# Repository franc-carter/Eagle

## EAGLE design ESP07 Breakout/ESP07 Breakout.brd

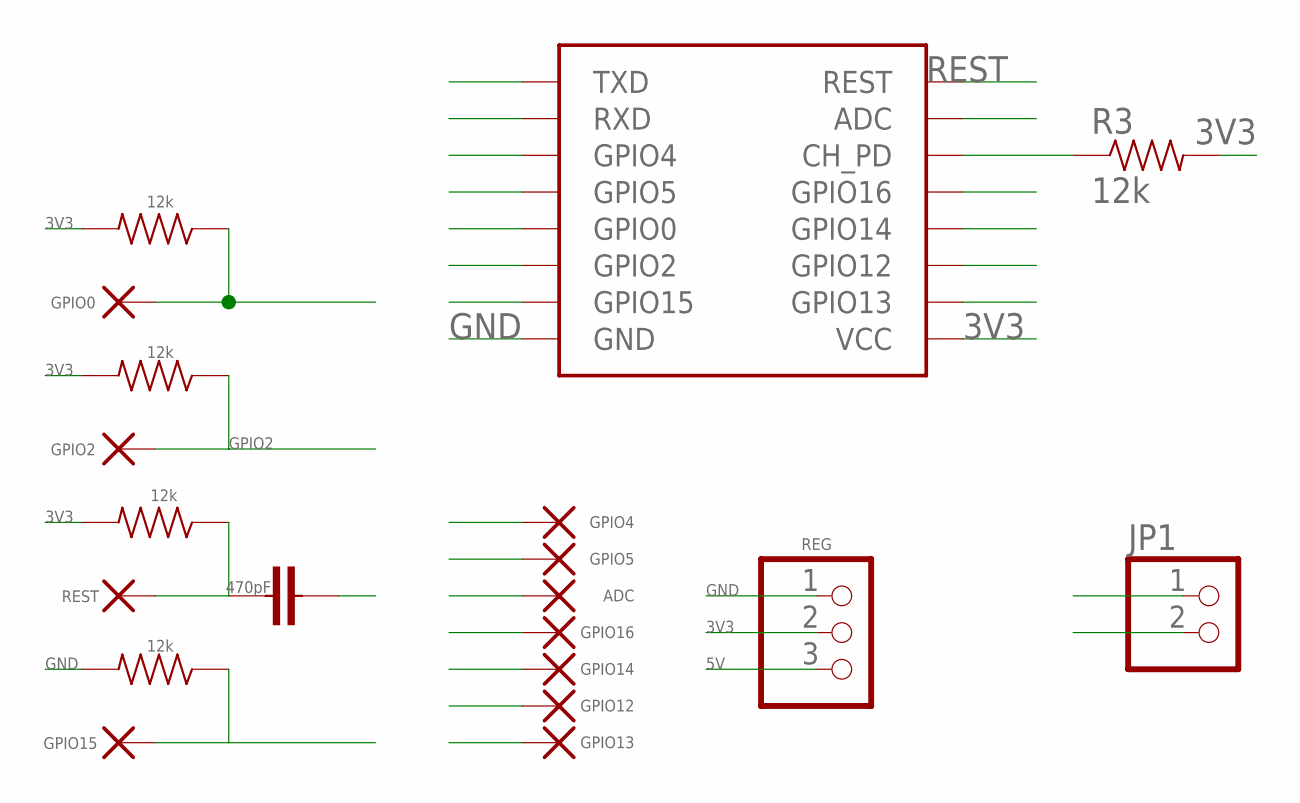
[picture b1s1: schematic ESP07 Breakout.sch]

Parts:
ADC: 1,6/0,8
C1: 470pF; 0603-CAP
GPIO0, GPIO2, GPIO4, GPIO5, GPIO12, GPIO13, GPIO14, GPIO15, GPIO16: 1,6/0,8
JP1: PINHD-1X2/90; 1X02/90
R1, R2, R3, R4, R5: 12k; 0603-RES
REG: PINHD-1X3; 1X03
REST: 1,6/0,8
U$1: ESP-07

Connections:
3V3: R1.2, R2.2, R3.2, R4.2, REG.2, U$1.VCC
5V: JP1.1, REG.3
ADC: ADC.1, U$1.ADC
GND: C1.2, JP1.2, R5.2, REG.1, U$1.GND
GPIO0: GPIO0.1, R1.1, U$1.GPIO00 (GPIO0)
GPIO2: GPIO2.1, R2.1, U$1.GPIO2
GPIO4: GPIO4.1, U$1.GPIO4
GPIO5: GPIO5.1, U$1.GPIO5
GPIO12: GPIO12.1, U$1.GPIO12
GPIO13: GPIO13.1, U$1.GPIO13
GPIO14: GPIO14.1, U$1.GPIO14
GPIO15: GPIO15.1, R5.1, U$1.GPIO15
GPIO16: GPIO16.1, U$1.GPIO16
unnamed: R3.1, U$1.CH_PD
REST: C1.1, R4.1, REST.1, U$1.REST
RXD: U$1.RXD
TXD: U$1.TXD

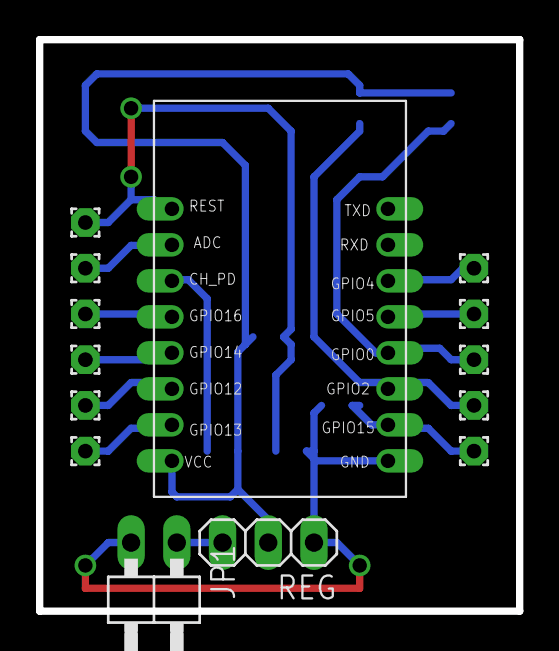
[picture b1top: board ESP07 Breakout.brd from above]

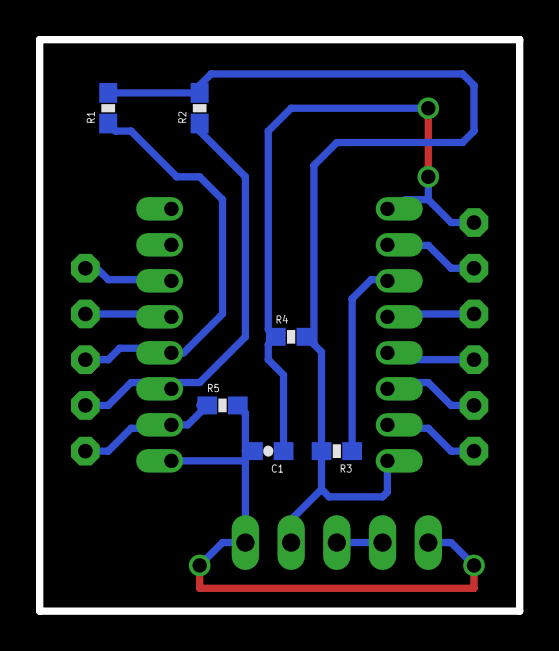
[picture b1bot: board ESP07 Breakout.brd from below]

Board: 2 copper layers, 26.7 x 31.8 mm, 20 parts (6 on the bottom side), 15 nets.

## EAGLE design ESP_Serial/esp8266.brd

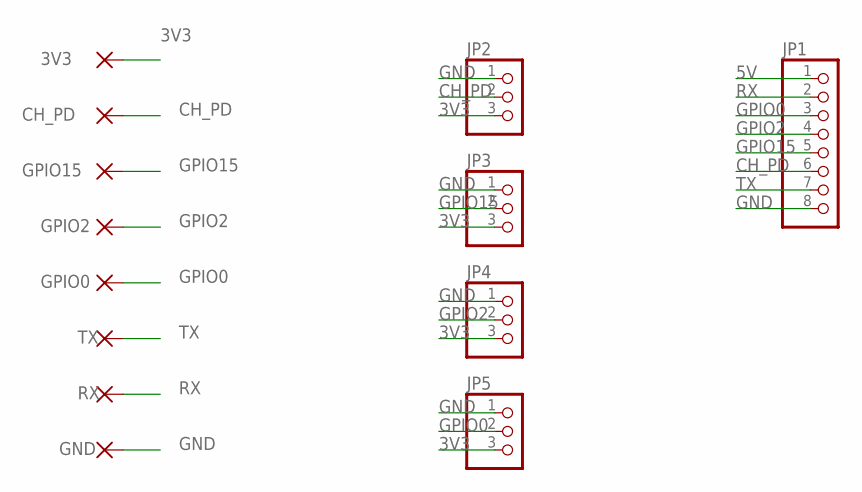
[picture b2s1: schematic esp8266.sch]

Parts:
3V3: 1,6/0,9
CH_PD: 1,6/0,9
GND: 1,6/0,9
GPIO0, GPIO2, GPIO15: 1,6/0,9
JP1: PINHD-1X8; 1X08
JP2, JP3, JP4, JP5: PINHD-1X3; 1X03
RX: 1,6/0,9
TX: 1,6/0,9

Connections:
3V3: 3V3.1, JP2.3, JP3.3, JP4.3, JP5.3
5V: JP1.1
CH_PD: CH_PD.1, JP1.6, JP2.2
GND: GND.1, JP1.8, JP2.1, JP3.1, JP4.1, JP5.1
GPIO0: GPIO0.1, JP1.3, JP5.2
GPIO2: GPIO2.1, JP1.4, JP4.2
GPIO15: GPIO15.1, JP1.5, JP3.2
RX: JP1.2, RX.1
TX: JP1.7, TX.1

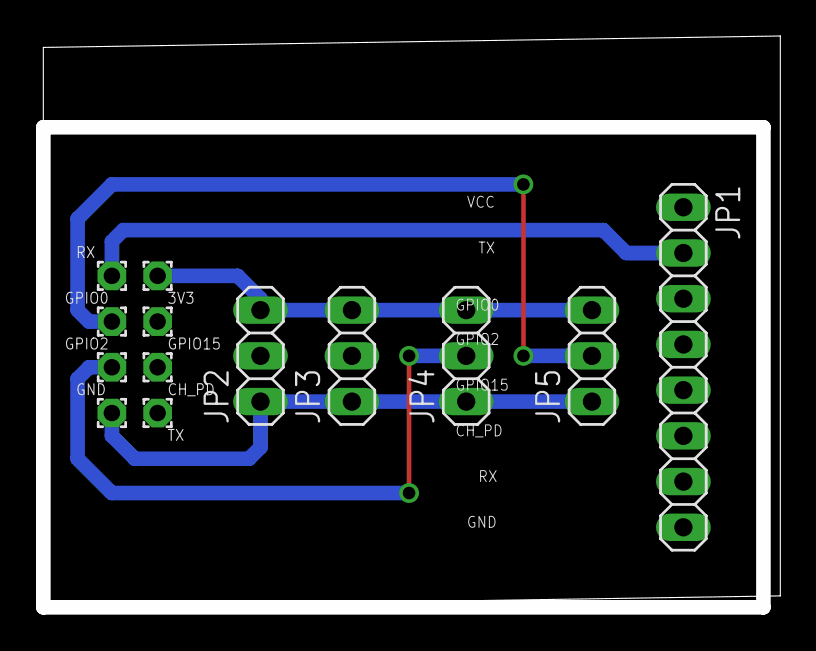
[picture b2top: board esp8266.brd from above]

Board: 2 copper layers, 40.9 x 31.7 mm, 13 parts (0 on the bottom side), 8 nets.

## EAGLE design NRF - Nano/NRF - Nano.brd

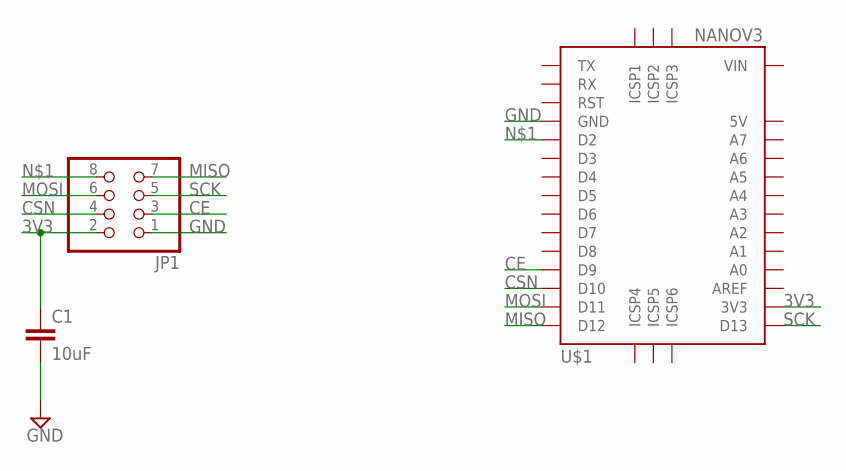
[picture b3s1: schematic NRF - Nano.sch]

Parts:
C1: 10uF; CAP-PTH-SMALL2
JP1: PINHD-2X4; 2X04
U$1: NANOV3

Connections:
3V3: C1.1, JP1.2, U$1.3V3
CE: JP1.3, U$1.D9
CSN: JP1.4, U$1.D10
GND: C1.2, JP1.1, U$1.GND1 (GND), U$1.GND2 (GND)
MISO: JP1.7, U$1.D12
MOSI: JP1.6, U$1.D11
unnamed: JP1.8, U$1.D2
SCK: JP1.5, U$1.D13
VIN: U$1.VIN

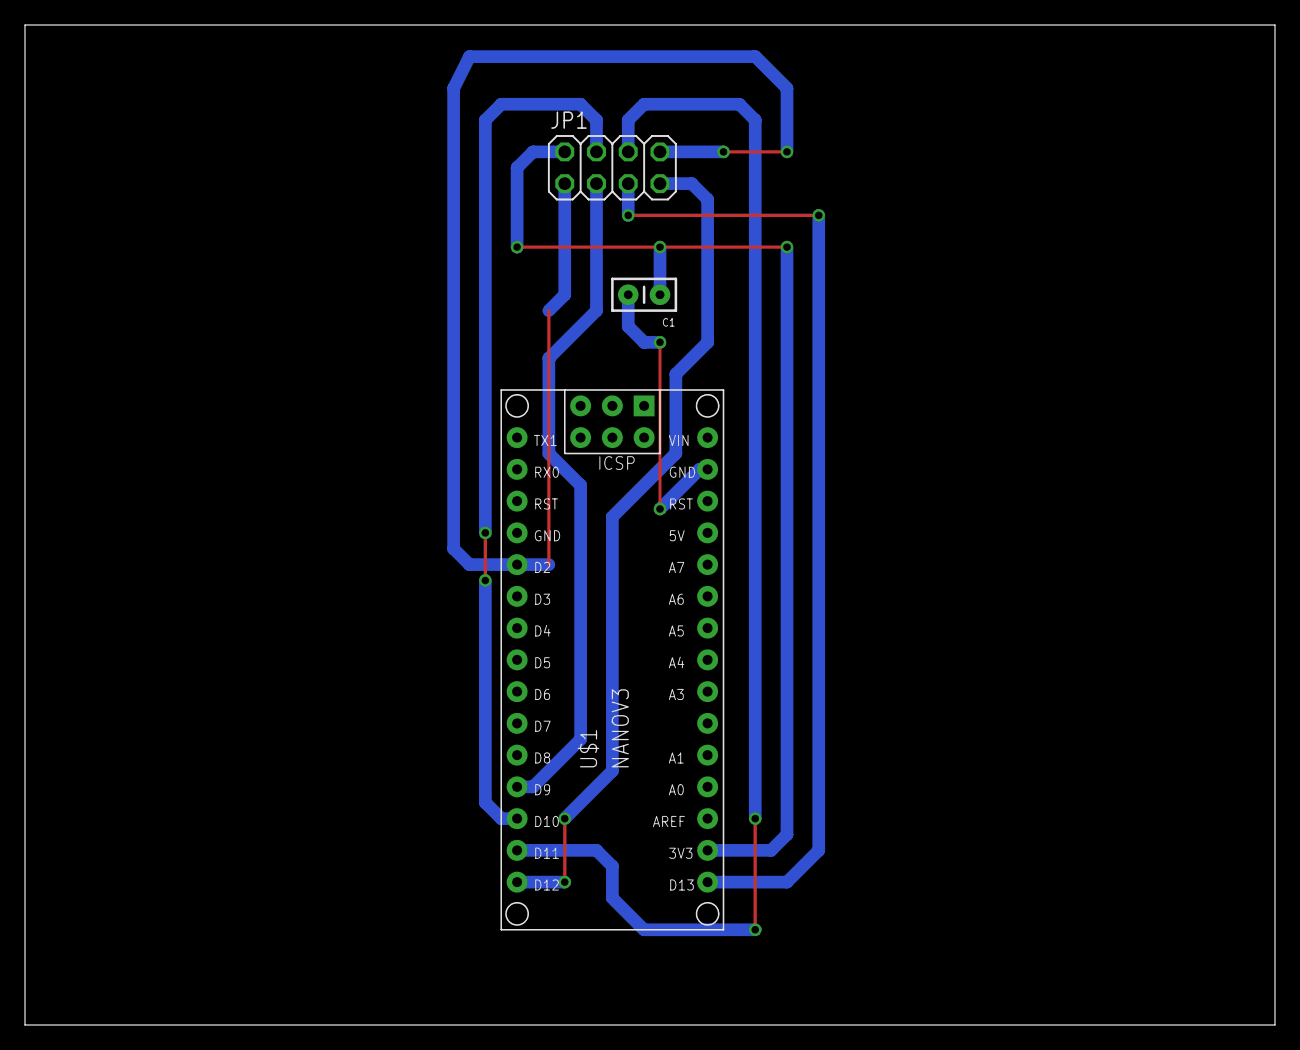
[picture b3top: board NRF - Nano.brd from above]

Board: 2 copper layers, 100.0 x 80.0 mm, 3 parts (0 on the bottom side), 8 nets.

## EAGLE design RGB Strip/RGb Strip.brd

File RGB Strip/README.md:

433MHz controlled RGB strip

A simple board that has a arduino nano, a 433mhz receiver and 3 mosfets to control an analogue rgb LED strip

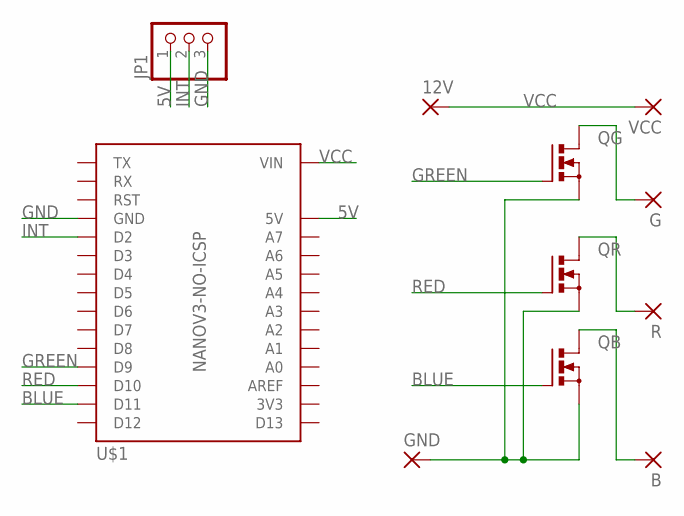
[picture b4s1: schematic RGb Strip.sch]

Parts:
12V: 1,6/0,9
B: 1,6/0,9
G: 1,6/0,9
GND: 1,6/0,9
JP1: PINHD-1X3; 1X03
QB: PMOSFET_NTO220BV; TO220BV
QG: PMOSFET_NTO220BV; TO220BV
QR: PMOSFET_NTO220BV; TO220BV
R: 1,6/0,9
U$1: NANOV3-NO-ICSP
VCC: 1,6/0,9

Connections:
5V: JP1.1, U$1.5V
BLUE: QB.G, U$1.D11
GND: GND.1, JP1.3, QB.S, QG.S, QR.S, U$1.GND@1 (GND), U$1.GND@2 (GND)
GREEN: QG.G, U$1.D9
INT: JP1.2, U$1.D2
unnamed: QR.D, R.1
unnamed: B.1, QB.D
unnamed: G.1, QG.D
RED: QR.G, U$1.D10
VCC: 12V.1, U$1.VIN, VCC.1

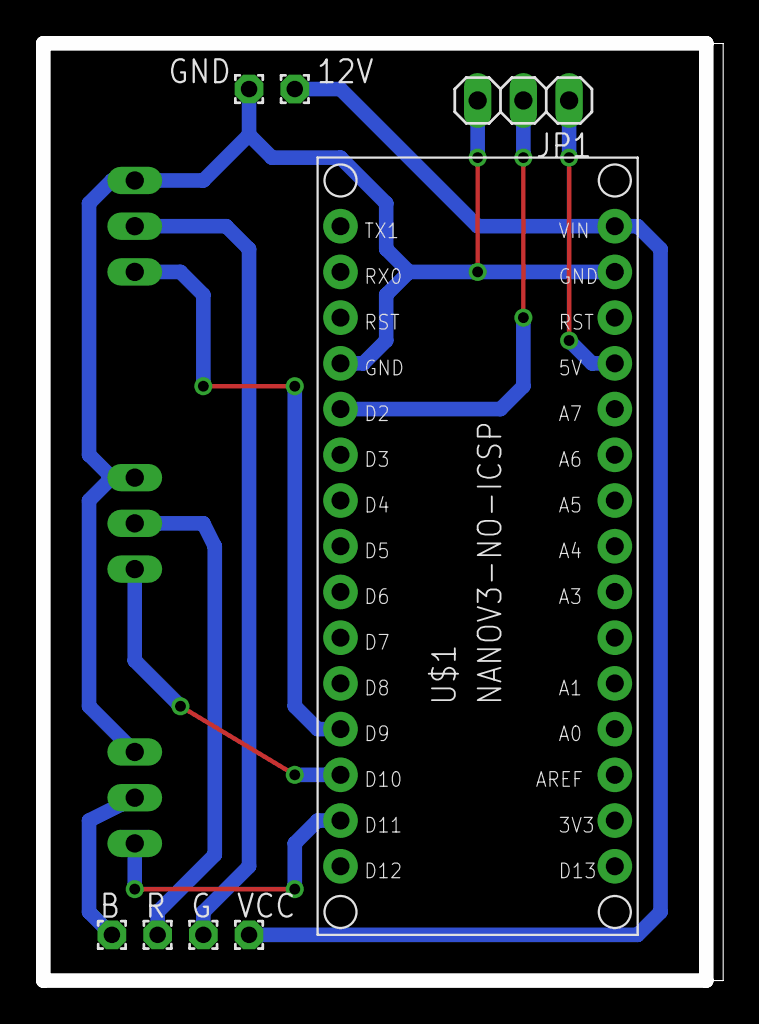
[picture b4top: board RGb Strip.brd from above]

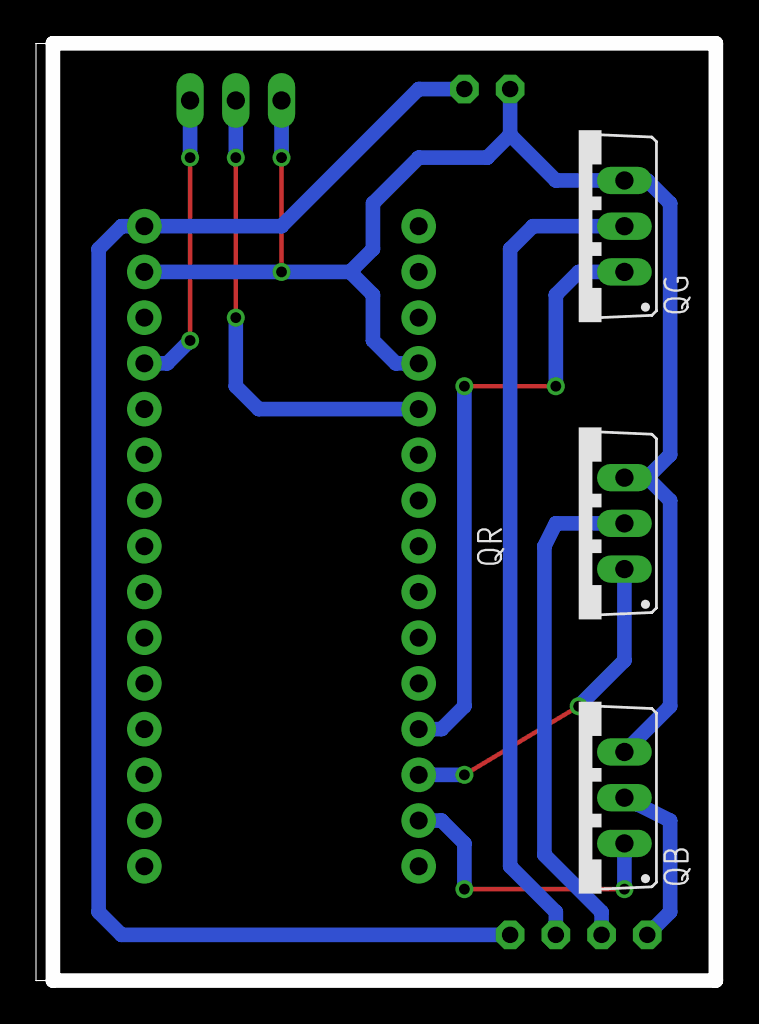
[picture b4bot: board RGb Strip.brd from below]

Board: 2 copper layers, 37.8 x 52.1 mm, 11 parts (3 on the bottom side), 10 nets.

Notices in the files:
parts and their libraries:
SparkFun-Passives: Licensing: Creative Commons ShareAlike 4.0 International - https://creativecommons.org/licenses/by-sa/4.0
